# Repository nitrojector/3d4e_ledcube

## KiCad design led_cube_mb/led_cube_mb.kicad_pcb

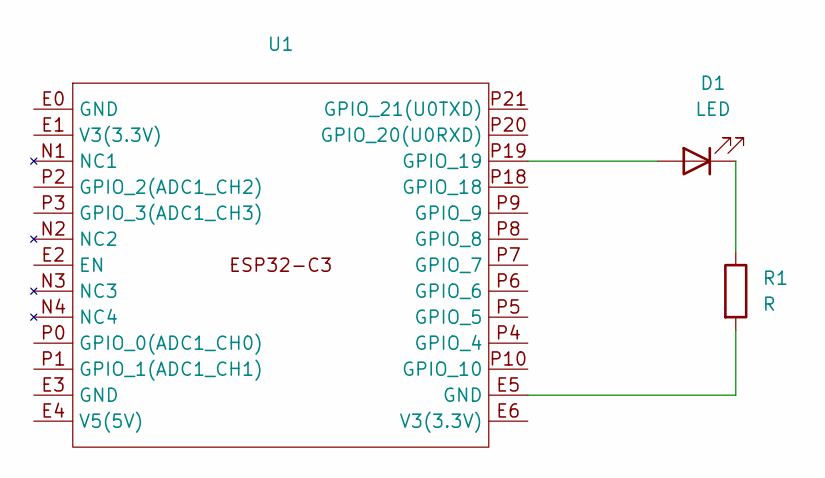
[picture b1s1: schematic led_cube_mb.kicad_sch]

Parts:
D1: LED; LED_D3.0mm_Horizontal_O6.35mm_Z10.0mm
R1: R; R_0402_1005Metric
U1: ESP32-C3

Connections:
unnamed: D1.2 (A), U1.P19 (GPIO_19)
unnamed: D1.1 (K), R1.1
unnamed: R1.2, U1.E5 (GND)

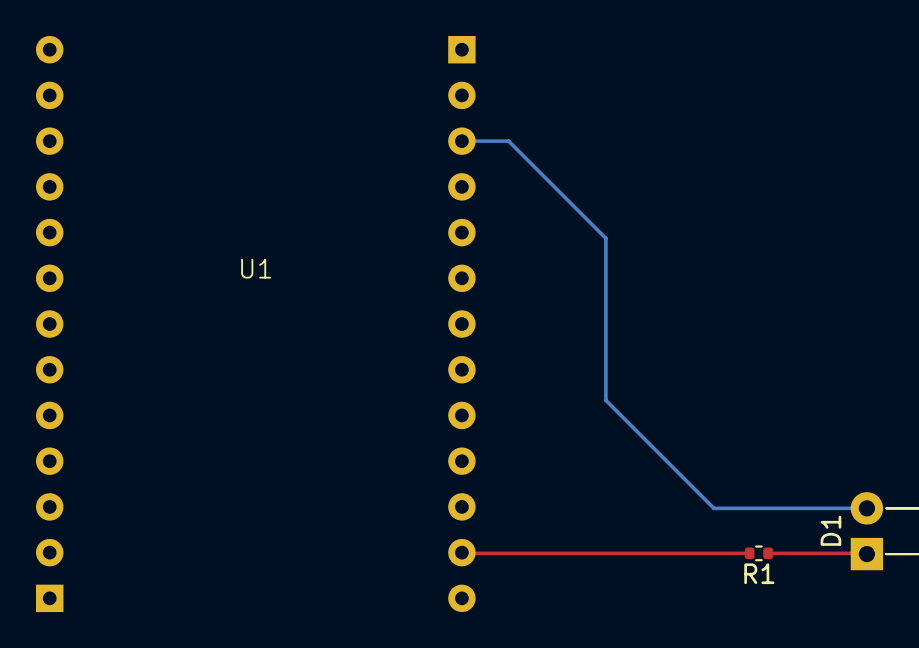
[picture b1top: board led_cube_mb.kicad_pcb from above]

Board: 2 copper layers, 3 parts (0 on the bottom side), 3 nets.

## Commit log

2024-10-24 Add ESP32
2025-01-10 Basic LED Demo
